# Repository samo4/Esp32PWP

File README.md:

# Esp32PWP

Inspiration:

https://circuitcellar.com/research-design-hub/basics-of-design/build-a-usb-c-power-supply/

# Bugs

- [ ] pinout is not the same (it's a **disaster**) as it should be according to [ESP-Prog](https://docs.espressif.com/projects/espressif-esp-dev-kits/en/latest/other/esp-prog/user_guide.html)

- [ ] routing for USB-C is far from optimum. See:

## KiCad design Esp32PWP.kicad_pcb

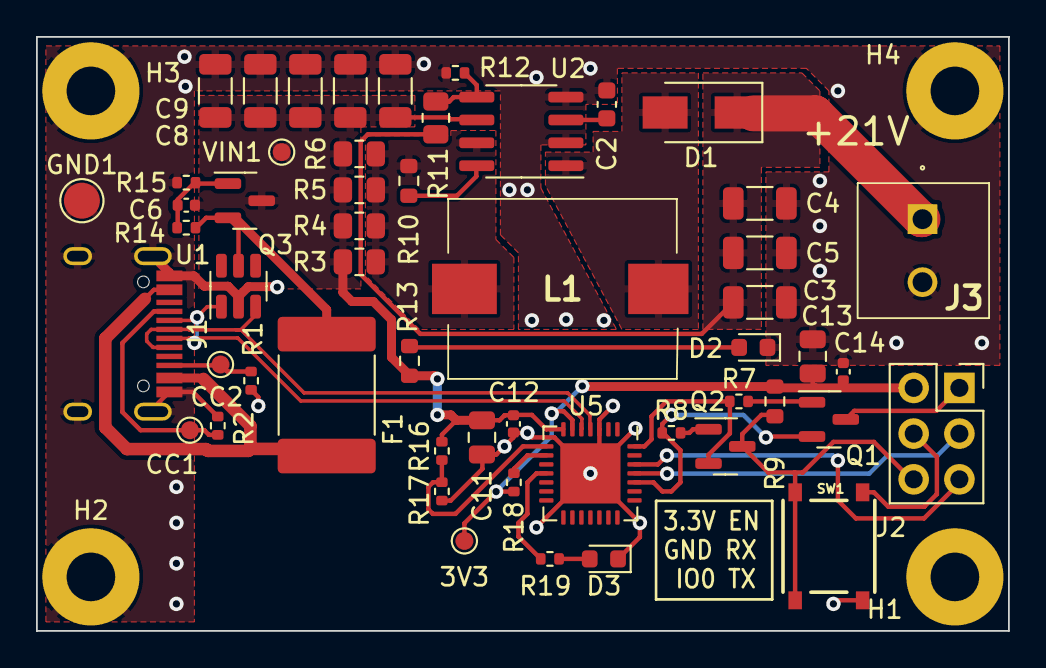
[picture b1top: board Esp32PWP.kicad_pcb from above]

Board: 2 copper layers, 54.0 x 33.0 mm, 57 parts (0 on the bottom side), 29 nets.

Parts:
3V3: TestPoint; TestPoint_Pad_D1.0mm
C1, C3, C4, C5, C7, C8, C9, C10: 22u/25V; C_1206_3216Metric
C2: 330p; C_0603_1608Metric
C6, C12, C14: 100n; C_0402_1005Metric
C11, C13: 2.2u; C_0805_2012Metric
CC1, CC2: TestPoint; TestPoint_Pad_D1.0mm
D1: D_Schottky; D_SMA
D2, D3: LED_GREEN; LED_0603_1608Metric
F1: 2920L150DR; Fuse_2920_7451Metric
GND1: TestPoint; TestPoint_Pad_D2.0mm
H1, H2, H3, H4: MountingHole_Pad; MountingHole_2.7mm_M2.5_Pad
J1: HRO-TYPE-C-31-M-12
J2: Conn_02x03_Odd_Even; PinSocket_2x03_P2.54mm_Vertical
J3: Conn_01x02; 1985807
L1: 47uH/1.6A; PM3316680MRC
Q1, Q2: MMBT3904; SOT-23
Q3: AO3401A; SOT-23
R1, R2: 5.1k; R_0402_1005Metric
R3, R4, R5, R6: 1R; R_0805_2012Metric
R7, R8: 10k; R_0402_1005Metric
R9: 10k; R_0603_1608Metric
R10: 180R; R_0603_1608Metric
R11: 20k; R_0805_2012Metric
R12: 1.2k; R_0402_1005Metric
R13: 2.7k; R_0603_1608Metric
R14: 100k; R_0402_1005Metric
R15, R18: 4k7; R_0402_1005Metric
R16: 22k; R_0402_1005Metric
R17: 47k; R_0402_1005Metric
R19: 220R; R_0402_1005Metric
SW1: SW_Push; TS-1187A-B-A-B
U1: SRV05-4; SOT-23-6
U2: MC34063AD; SOIC-8_3.9x4.9mm_P1.27mm
U5: CP2102N-Axx-xQFN28; QFN-28-1EP_5x5mm_P0.5mm_EP3.35x3.35mm
VIN1: TestPoint; TestPoint_Pad_D1.0mm

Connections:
+3V3: 3V3.1, C13.1, C14.1, J2.2, R9.1, R18.1, U5.6 (VDD)
+24V: C3.1, C4.1, C5.1, D1.1 (K), J3.1, R11.1
/CC1: CC1.1, J1.A5 (CC1), R2.1
/CC2: CC2.1, J1.B5 (CC2), R1.1
/USB2serial/CHIP_PU: J2.1, Q1.3 (C)
/USB2serial/DTR: Q2.2 (E), R7.2, U5.28 (~DTR)
/USB2serial/IO0: J2.6, Q2.3 (C), R9.2, SW1.2
/USB2serial/RTS: Q1.2 (E), R8.2, U5.24 (~RTS)
/USB2serial/RX: J2.3, U5.25 (RXD)
/USB2serial/TX: J2.5, U5.26 (TXD)
GND: C1.2, C2.2, C3.2, C4.2, C5.2, C7.2, C8.2, C9.2, C10.2, C11.2, C12.2, C13.2, C14.2, D2.1 (K), D3.1 (K), GND1.1, H1.1, H2.1, H3.1, H4.1, J1.A1 (GND), J1.A12 (GND), J1.S1 (SHIELD), J2.4, J3.2, R1.2, R2.2, R12.2, R15.2, R17.2, SW1.1, U1.2 (VN), U2.2 (SwE), U2.4 (GND), U5.3 (GND), U5.29 (GND)
unnamed: C2.1, U2.3 (TC)
unnamed: C6.2, Q3.1 (G), R14.2, R15.1
unnamed: D1.2 (A), L1.2, U2.1 (SwC)
unnamed: D2.2 (A), R13.2
unnamed: D3.2 (A), R19.2
unnamed: F1.2, J1.A4 (VBUS), J1.B9 (VBUS)
unnamed: L1.1, R3.1, R4.1, R5.1, R6.1, R10.1, U2.7 (Ipk)
unnamed: Q1.1 (B), R7.1
unnamed: Q2.1 (B), R8.1
unnamed: R10.2, U2.8 (DC)
unnamed: R11.2, R12.1, U2.5 (Vfb)
unnamed: R16.2, R17.1, U5.8 (VBUS)
unnamed: R18.2, U5.9 (~RST)
unnamed: R19.1, U5.11 (~SUSPEND)
USB_D+: J1.A6 (D+), J1.B6 (D+), U1.3 (IO2), U5.4 (D+)
USB_D-: J1.A7 (D-), J1.B7 (D-), U1.1 (IO1), U5.5 (D-)
VBUS: F1.1, Q3.2 (S), R14.1, U1.5 (VP)
VIN: C1.1, C6.1, C7.1, C8.1, C9.1, C10.1, C11.1, C12.1, Q3.3 (D), R3.2, R4.2, R5.2, R6.2, R13.1, R16.1, U2.6 (Vin), U5.7 (VREGIN), VIN1.1

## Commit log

2022-09-25 add inps
2022-09-25 smth
2022-09-30 feature creep
2022-10-01 ready for JLCPCB
2022-10-04 this was sent to jlcpcb
2022-12-09 bugs
2023-02-27 disaster
2023-10-31 7.0.8
2023-10-31 removed lck
